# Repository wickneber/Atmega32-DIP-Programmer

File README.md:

# Atmega32-DIP-Programmer
This is a basic PCB programmer for the ATMEGA32 mcu.
This is my first attempt at designing a PCB.

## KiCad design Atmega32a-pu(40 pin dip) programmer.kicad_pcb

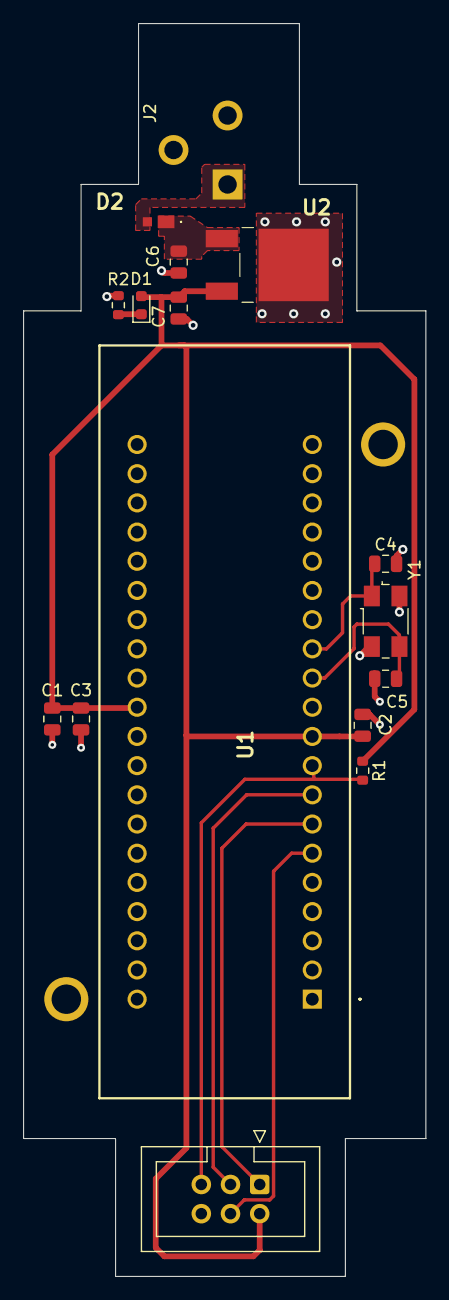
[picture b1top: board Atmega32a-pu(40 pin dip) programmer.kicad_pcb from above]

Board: 2 copper layers, 35.0 x 109.0 mm, 16 parts (0 on the bottom side), 11 nets.

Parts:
C1: 10uf; C_0805_2012Metric
C2, C3: 100nf; C_0805_2012Metric
C4, C5: 14pf; C_0805_2012Metric
C6: 33uf; C_0805_2012Metric
C7: 0.1uf; C_0805_2012Metric
D1: LED; LED_0603_1608Metric
D2: D; RBR2VWM40ATFTR
J1: AVR-ISP-6; IDC-Header_2x03_P2.54mm_Vertical
J2: Barrel_Jack_Switch; BarrelJack_CUI_PJ-102AH_Horizontal
R1: 10k; R_0603_1608Metric
R2: 100; R_0603_1608Metric
U1: ATmega32-16P; 2401280390602J
U2: L7805ABD2T-TR; L7805CDTTR
Y1: 8MHZ; Crystal_SMD_0603-4Pin_6.0x3.5mm

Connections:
+5V: C1.1, C2.1, C3.1, C7.1, D1.2 (A), J1.2 (VCC), R1.1, U1.10 (VCC), U1.30 (AVCC), U2.3 (OUT)
/MISO: J1.1 (MISO), U1.7 (PB6)
/MOSI: J1.4 (MOSI), U1.6 (PB5)
/RST: J1.5 (~RST), R1.2, U1.9 (~RESET)
/SCK: J1.3 (SCK), U1.8 (PB7)
GND: C1.2, C2.2, C3.2, C4.2, C5.2, C6.2, C7.2, J1.6 (GND), J2.2, J2.3, R2.1, U1.11 (GND), U1.31 (GND), U2.2 (GND), Y1.2, Y1.4
unnamed: C4.1, U1.13 (XTAL1), Y1.1
unnamed: C5.1, U1.12 (XTAL2), Y1.3
unnamed: D1.1 (K), R2.2
VCC: C6.1, D2.1 (K), U2.1 (IN)
VDD: D2.2 (A), J2.1
